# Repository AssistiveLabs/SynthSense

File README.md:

##SynthSense

####Team
Craig Hiller, Frank Lu, Adithya Murali, Krishna Parashar, Tomás Vega

####Course
Interactive Device Design, fall 2015

Aimed at empowering the visually impaired by augmenting their awareness of the environment and facilitating independence, SynthSense is an open-source Augmented White Cane (AWC) that provides both obstacle avoidance and navigation assistance.

To help with obstacle avoidance, the team built a cane with ultrasonic range finders for detecting obstacles within a two-meter range as well as mounts for the sensors that are both direction- and height-adjustable. Feedback from these sensors deliver haptic responses on the handle when obstacles are detected at body or head level.

To provide navigation instructions to users, the SynthSense team developed an iOS app that determines when the user needs to turn. The app transmits a command to the AWC’s strap, providing directional haptic feedback that the user can act on.

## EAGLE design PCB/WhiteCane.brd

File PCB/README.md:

#SynthSense PCB

---

###Components
- [RFduino](http://www.rfduino.com/wp-content/uploads/2015/08/RFD22301.Data.Sheet.08.20.15_4.36PM.pdf)
- [IO Extender (MCP32008)](http://ww1.microchip.com/downloads/en/DeviceDoc/21919e.pdf)
- [SparkFun Power Cell - LiPo Charger/Booster](https://www.sparkfun.com/products/11231)

###Inputs
- [2x Ultrasonic Range Finder (HC-SR04)](http://www.amazon.com/SainSmart-HC-SR04-Ranging-Detector-Distance/dp/B004U8TOE6)

###Outputs
- [6x 12mm x 3.4mm coin motor](http://www.amazon.com/Voltage-Vibration-Micro-Motor-Phone/dp/B00NP4ARF6/)
  - Voltage: 1.5v-3v
  - Continuous Current: 55mA

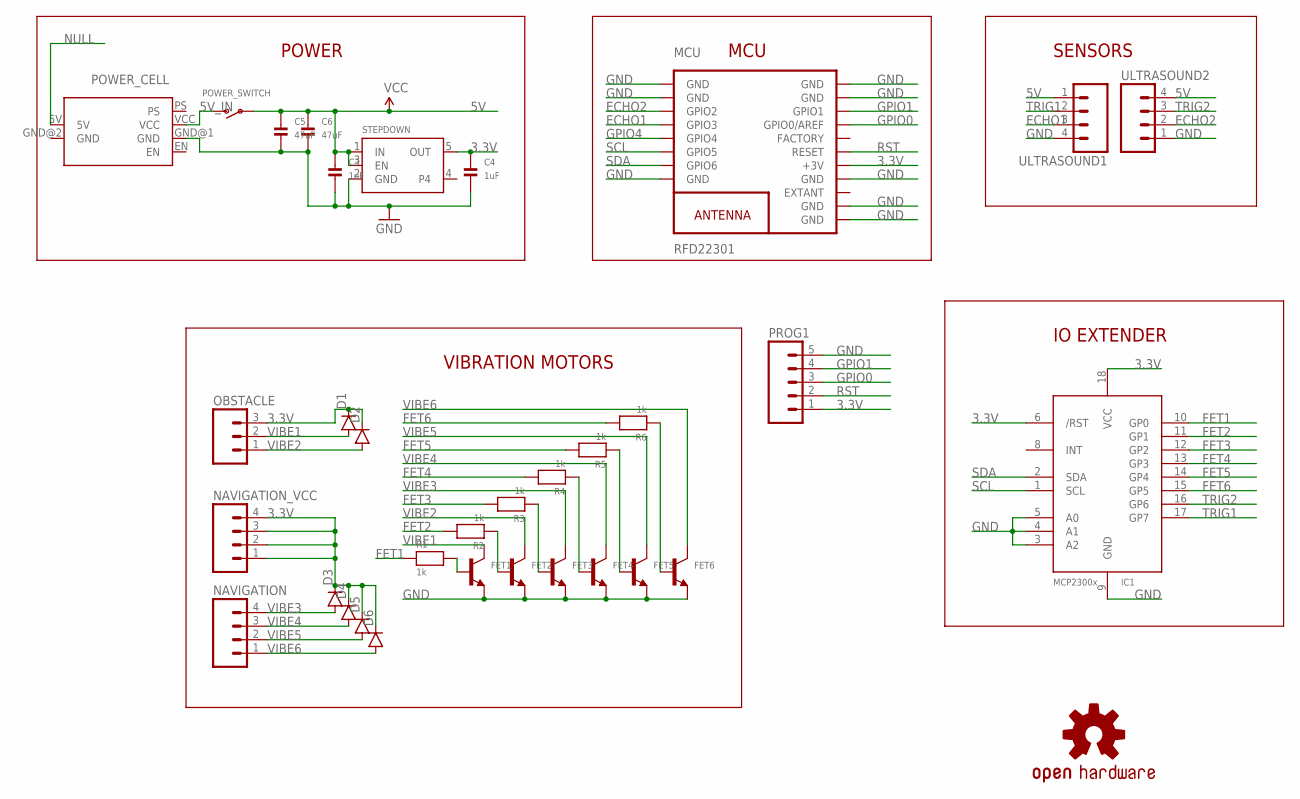
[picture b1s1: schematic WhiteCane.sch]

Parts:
C3, C4: 1uF; 0603
C5, C6: 47uF; 0805
D1, D2, D3, D4, D5, D6: DIODESOD123; SOD-123
FET1, FET2, FET3, FET4, FET5, FET6: TRANSISTOR_NPN; SOT23-R
IC1: MCP23008/SO; SO18W
LOGO1: OSHW-LOGOL-COPPER; OSHW-LOGO-L_COPPER
MCU: RFD22301
NAVIGATION: M04PTH; 1X04
NAVIGATION_VCC: M04PTH; 1X04
OBSTACLE: M03PTH; 1X03
POWER_CELL: POWER_CELL
POWER_SWITCH: SWITCH_SPST; SPST_SMT_19192
PROG1: M05PTH; 1X05
R1, R2, R3, R4, R5, R6: 1k; 0603
STEPDOWN: VREG_SOT23-5; SOT23-5
ULTRASOUND1, ULTRASOUND2: M04PTH; 1X04

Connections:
3.3V: C4.1, D1.C, D2.C, D3.C, D4.C, D5.C, D6.C, IC1.6 (/RST), IC1.18 (VCC), MCU.13 (+3V), NAVIGATION_VCC.1, NAVIGATION_VCC.2, NAVIGATION_VCC.3, NAVIGATION_VCC.4, OBSTACLE.3, PROG1.1, STEPDOWN.5 (OUT)
5V: C3.1, C5.1, C6.1, POWER_SWITCH.B, STEPDOWN.1 (IN), STEPDOWN.3 (EN), ULTRASOUND1.1, ULTRASOUND2.4
5V_IN: POWER_CELL.VCC, POWER_SWITCH.C (S)
ECHO1: MCU.4 (GPIO3), ULTRASOUND1.3
ECHO2: MCU.3 (GPIO2), ULTRASOUND2.2
FET1: IC1.10 (GP0), R1.1
FET2: IC1.11 (GP1), R2.2
FET3: IC1.12 (GP2), R3.2
FET4: IC1.13 (GP3), R4.2
FET5: IC1.14 (GP4), R5.2
FET6: IC1.15 (GP5), R6.2
GND: C3.2, C4.2, C5.2, C6.2, FET1.2 (E), FET2.2 (E), FET3.2 (E), FET4.2 (E), FET5.2 (E), FET6.2 (E), IC1.3 (A2), IC1.4 (A1), IC1.5 (A0), IC1.9 (GND), MCU.1 (GND), MCU.2 (GND), MCU.8 (GND), MCU.9 (GND), MCU.10 (GND), MCU.12 (GND), MCU.18 (GND), MCU.19 (GND), POWER_CELL.GND@1 (GND), POWER_CELL.GND@2 (GND), PROG1.5, STEPDOWN.2 (GND), ULTRASOUND1.4, ULTRASOUND2.1
GPIO0: MCU.16 (GPIO0/AREF), PROG1.3
GPIO1: MCU.17 (GPIO1), PROG1.4
GPIO4: MCU.5 (GPIO4)
unnamed: FET1.1 (B), R1.2
unnamed: FET2.1 (B), R2.1
unnamed: FET3.1 (B), R3.1
unnamed: FET4.1 (B), R4.1
unnamed: FET5.1 (B), R5.1
unnamed: FET6.1 (B), R6.1
NULL: POWER_CELL.5V
RST: MCU.14 (RESET), PROG1.2
SCL: IC1.1 (SCL), MCU.6 (GPIO5)
SDA: IC1.2 (SDA), MCU.7 (GPIO6)
TRIG1: IC1.17 (GP7), ULTRASOUND1.2
TRIG2: IC1.16 (GP6), ULTRASOUND2.3
VIBE1: D1.A, FET1.3 (C), OBSTACLE.2
VIBE2: D2.A, FET2.3 (C), OBSTACLE.1
VIBE3: D3.A, FET3.3 (C), NAVIGATION.4
VIBE4: D4.A, FET4.3 (C), NAVIGATION.3
VIBE5: D5.A, FET5.3 (C), NAVIGATION.2
VIBE6: D6.A, FET6.3 (C), NAVIGATION.1

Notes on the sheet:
VIBRATION MOTORS
POWER
SENSORS
IO EXTENDER
MCU

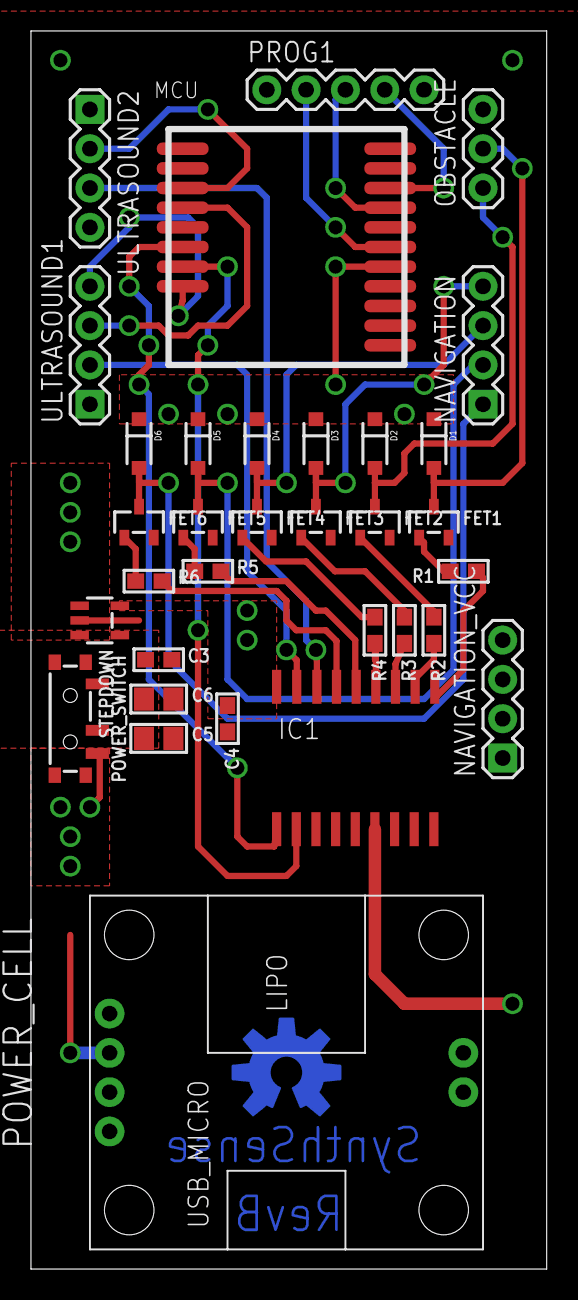
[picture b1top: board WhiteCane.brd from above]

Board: 2 copper layers, 33.3 x 80.0 mm, 34 parts (0 on the bottom side), 31 nets.

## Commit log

2016-02-23 cloned from Synthloned from SynthSense"

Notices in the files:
parts and their libraries:
microbuilder: This work is placed in the public domain, and may be freely used for commercial and non-commercial work with the following conditions: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
SparkFun-DiscreteSemi: Licensing: Creative Commons ShareAlike 4.0 International - https://creativecommons.org/licenses/by-sa/4.0
